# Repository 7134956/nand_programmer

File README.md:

# NANDO (NANDopen) programmer

## General
NANDO is open source NAND programmer based on low cost MCU CH32V307VCT6. It supports parallel NAND, SPI NOR, SPI NAND programming.
High programming speed! For examle EM73C044SNB (1Gb) Write 110(s), Read 80(s).

PCB boards:

Application:

## Features
- USB_HS interface
- PC client software for Linux & Windows.
- TSOP-48 socket for NAND chip
- 8 bit parallel NAND interface
- SPI interface
- 3.3V NAND power supply
- NAND read,write and erase support
- NAND read of chip ID support
- NAND read of bad blocks
- NAND bad block skip option
- NAND include spare area option
- Configurable erase, write, read areas.
- Open KiCad PCB & Schematic
- Open source code
- Read & Write LEDs indication
- Extendable chip database
- Chip autodetection
- Firmware update

### Supported chips
#### Parallel NAND:
K9F2G08U0C, HY27US08121B, TC58NVG2S3E, F59L2G81A, MX30LF2G18AC and others.

See full list of supported chips [qt/nando_parallel_chip_db.csv](qt/nando_parallel_chip_db.csv)

#### SPI NOR flash
AT45DB021D, MX25L8006E, W25Q16JV and others.

See full list of supported chips [qt/nando_spi_nor_db.csv](qt/nando_spi_nor_db.csv)

#### SPI NAND flash
GD5F1GQ4UBxIG, MT29F2G01, F50L2G41LB and others.

See full list of supported chips [qt/nando_spi_nand_db.csv](qt/nando_spi_nand_db.csv)

## Release binaries
...

### License
In general the sorce code, PCB and schematic are under GPLv3 license but with limitations of:

## WiKi
Check [WiKi](https://github.com/bbogush/nand_programmer/wiki) page for more information.

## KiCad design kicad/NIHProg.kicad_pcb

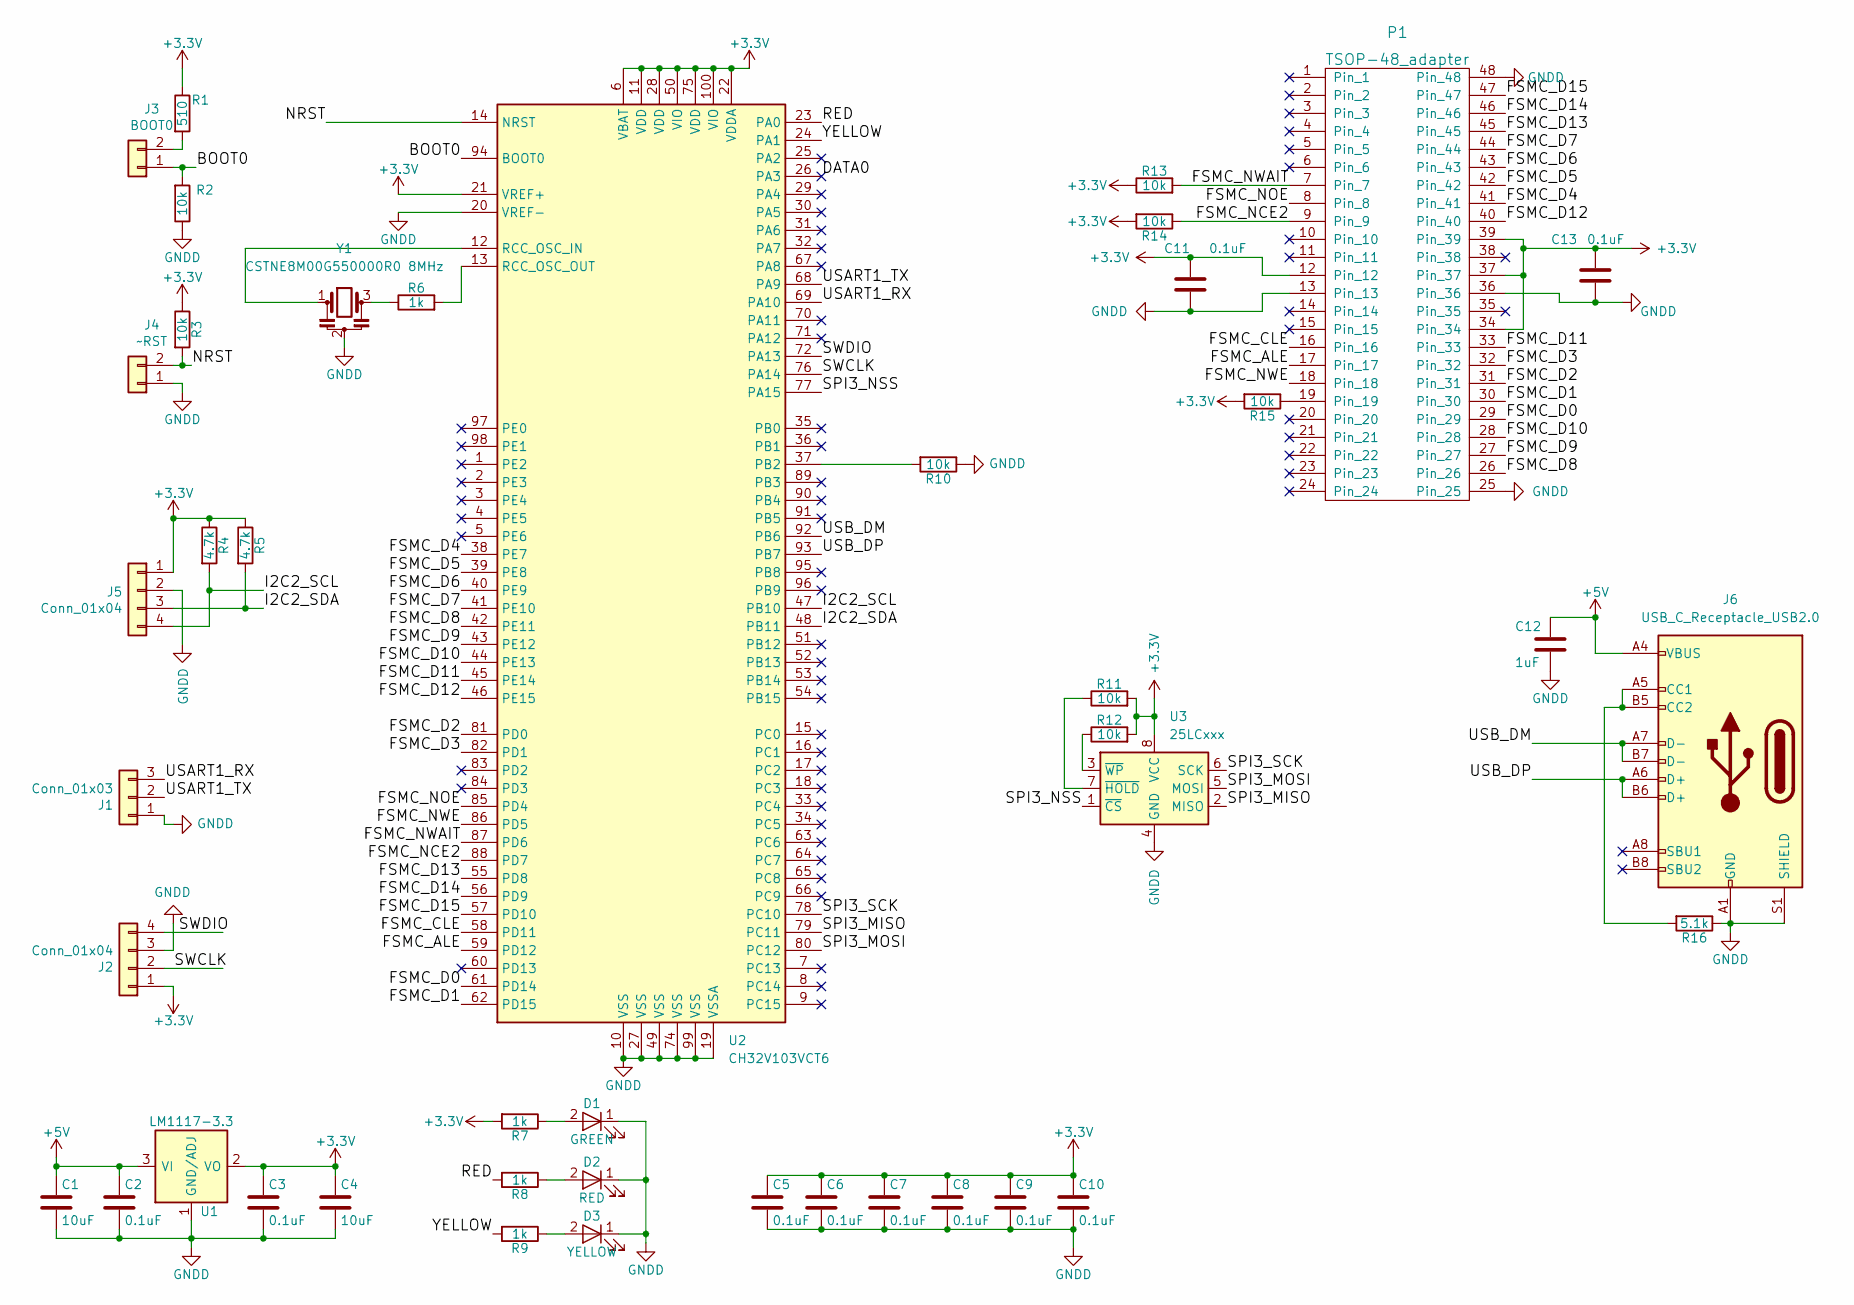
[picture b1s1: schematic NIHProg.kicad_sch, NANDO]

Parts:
C1, C4: 10uF; C_0805_2012Metric_Pad1.18x1.45mm_HandSolder; Farnell Ref 2112850
C2, C3, C5, C6, C7, C8, C9, C10, C11, C13: 0.1uF; C_0603_1608Metric_Pad1.08x0.95mm_HandSolder; Farnell Ref 2320839
C12: 1uF; C_0603_1608Metric_Pad1.08x0.95mm_HandSolder; Farnell Ref 2320839
D1: GREEN; LED_0603_1608Metric_Pad1.05x0.95mm_HandSolder; Farnell Ref 2099239
D2: RED; LED_0603_1608Metric_Pad1.05x0.95mm_HandSolder; Farnell Ref 2099236
D3: YELLOW; LED_0603_1608Metric_Pad1.05x0.95mm_HandSolder; Farnell Ref 2099243
J1: Conn_01x03; PinHeader_1x03_P2.54mm_Vertical; Farnell Ref 3049527
J2, J5: Conn_01x04; PinHeader_1x04_P2.54mm_Vertical; Farnell Ref 3049529
J3: BOOT0; SolderJumper-2_P1.3mm_Open_RoundedPad1.0x1.5mm
J4: ~RST; SolderJumper-2_P1.3mm_Open_RoundedPad1.0x1.5mm
J6: USB_C_Receptacle_USB2.0; TYPE-C-31-M-12; MPN TYPE-C-31-M-17
P1: TSOP-48_adapter; TSOP48ZIF
R1: 510; R_0603_1608Metric_Pad0.98x0.95mm_HandSolder; Farnell Ref 2447679
R2, R3, R10, R11, R12, R13, R14, R15: 10k; R_0603_1608Metric_Pad0.98x0.95mm_HandSolder; Farnell Ref 2447553
R4, R5: 4.7k; R_0603_1608Metric_Pad0.98x0.95mm_HandSolder; Farnell Ref 2447553
R6: 1k; R_0603_1608Metric_Pad0.98x0.95mm_HandSolder; Farnell Ref 2447553
R7, R8, R9: 1k; R_0603_1608Metric_Pad0.98x0.95mm_HandSolder; Farnell Ref 2447587
R16: 5.1k; R_0603_1608Metric_Pad0.98x0.95mm_HandSolder; Farnell Ref 2447587
U1: LM1117-3.3; SOT-223; Farnell Ref 3007498
U2: CH32V103VCT6; LQFP-100_14x14mm_P0.5mm
U3: 25LCxxx; DIP-8_W7.62mm_Socket
Y1: CSTNE8M00G550000R0 8MHz; Resonator_SMD_Murata_CSTxExxV-3Pin_3.0x1.1mm_HandSoldering

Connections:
+3V3: C3.1, C4.1, C5.1, C6.1, C7.1, C8.1, C9.1, C10.1, C11.1, C13.1, J2.1, J5.1, P1.12, P1.34, P1.37, P1.39, R1.1, R3.1, R4.1, R5.1, R7.2, R11.2, R12.2, R13.1, R14.2, R15.2, U1.2 (VO), U1.4 (VO), U2.6 (VBAT), U2.11 (VDD), U2.21 (VREF+), U2.22 (VDDA), U2.28 (VDD), U2.50 (VIO), U2.75 (VDD), U2.100 (VIO), U3.8 (VCC)
+5V: C1.1, C2.1, C12.1, J6.A4 (VBUS), J6.A9 (VBUS), J6.B4 (VBUS), J6.B9 (VBUS), U1.3 (VI)
/BOOT0: J3.1, R2.2, U2.94 (BOOT0)
/DATA0: U2.26 (PA3)
/FSMC_ALE: P1.17, U2.59 (PD12)
/FSMC_CLE: P1.16, U2.58 (PD11)
/FSMC_D0: P1.29, U2.61 (PD14)
/FSMC_D1: P1.30, U2.62 (PD15)
/FSMC_D2: P1.31, U2.81 (PD0)
/FSMC_D3: P1.32, U2.82 (PD1)
/FSMC_D4: P1.41, U2.38 (PE7)
/FSMC_D5: P1.42, U2.39 (PE8)
/FSMC_D6: P1.43, U2.40 (PE9)
/FSMC_D7: P1.44, U2.41 (PE10)
/FSMC_D8: P1.26, U2.42 (PE11)
/FSMC_D9: P1.27, U2.43 (PE12)
/FSMC_D10: P1.28, U2.44 (PE13)
/FSMC_D11: P1.33, U2.45 (PE14)
/FSMC_D12: P1.40, U2.46 (PE15)
/FSMC_D13: P1.45, U2.55 (PD8)
/FSMC_D14: P1.46, U2.56 (PD9)
/FSMC_D15: P1.47, U2.57 (PD10)
/FSMC_NCE2: P1.9, R14.1, U2.88 (PD7)
/FSMC_NOE: P1.8, U2.85 (PD4)
/FSMC_NWAIT: P1.7, R13.2, U2.87 (PD6)
/FSMC_NWE: P1.18, U2.86 (PD5)
/I2C2_SCL: J5.4, R4.2, U2.47 (PB10)
/I2C2_SDA: J5.3, R5.2, U2.48 (PB11)
/NRST: J4.2, R3.2, U2.14 (NRST)
/RED: R8.2, U2.23 (PA0)
/SPI3_MISO: U2.79 (PC11), U3.2 (MISO)
/SPI3_MOSI: U2.80 (PC12), U3.5 (MOSI)
/SPI3_NSS: U2.77 (PA15), U3.1 (~CS)
/SPI3_SCK: U2.78 (PC10), U3.6 (SCK)
/SWCLK: J2.2, U2.76 (PA14)
/SWDIO: J2.4, U2.72 (PA13)
/USART1_RX: J1.3, U2.69 (PA10)
/USART1_TX: J1.2, U2.68 (PA9)
/USB_DM: J6.A7 (D-), J6.B7 (D-), U2.92 (PB6)
/USB_DP: J6.A6 (D+), J6.B6 (D+), U2.93 (PB7)
/YELLOW: R9.2, U2.24 (PA1)
GNDD: C1.2, C2.2, C3.2, C4.2, C5.2, C6.2, C7.2, C8.2, C9.2, C10.2, C11.2, C12.2, C13.2, D1.1 (K), D2.1 (K), D3.1 (K), J1.1, J2.3, J4.1, J5.2, J6.A1 (GND), J6.A12 (GND), J6.B1 (GND), J6.B12 (GND), J6.S1 (SHIELD), P1.13, P1.25, P1.36, P1.48, R2.1, R10.1, R16.1, U1.1 (GND/ADJ), U2.10 (VSS), U2.19 (VSSA), U2.20 (VREF-), U2.27 (VSS), U2.49 (VSS), U2.74 (VSS), U2.99 (VSS), U3.4 (GND), Y1.2
unnamed: D1.2 (A), R7.1
unnamed: D2.2 (A), R8.1
unnamed: D3.2 (A), R9.1
unnamed: J3.2, R1.2
unnamed: J6.A5 (CC1), J6.B5 (CC2), R16.2
unnamed: P1.19, R15.1
unnamed: R6.1, Y1.3
unnamed: R6.2, U2.13 (RCC_OSC_OUT)
unnamed: R10.2, U2.37 (PB2)
unnamed: R11.1, U3.7 (~HOLD)
unnamed: R12.1, U3.3 (~WP)
unnamed: U2.12 (RCC_OSC_IN), Y1.1

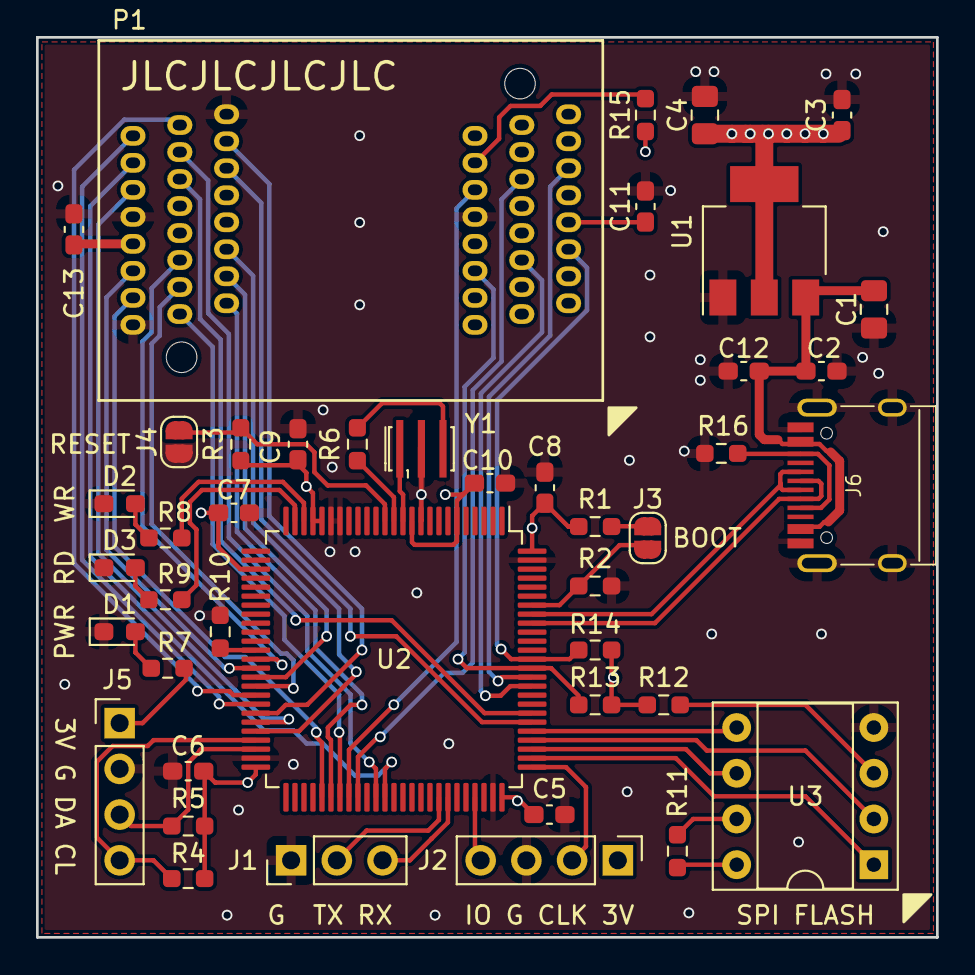
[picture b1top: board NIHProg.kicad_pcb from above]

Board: 4 copper layers, 50.0 x 50.0 mm, 43 parts (0 on the bottom side), 53 nets.

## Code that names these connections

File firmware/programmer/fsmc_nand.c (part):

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    RCC_APB2PeriphClockCmd(RCC_APB2Periph_GPIOD | RCC_APB2Periph_GPIOE, ENABLE);

    gpio_init.GPIO_Pin =
		GPIO_Pin_0		//FSMC_D2
		| GPIO_Pin_1	//FSMC_D3
		| GPIO_Pin_4	//FSMC_NOE
		| GPIO_Pin_5	//FSMC_NWE
		| GPIO_Pin_7	//FSMC_NCE2
		| GPIO_Pin_8	//FSMC_D13
		| GPIO_Pin_9	//FSMC_D14
		| GPIO_Pin_10	//FSMC_D15
		| GPIO_Pin_11	//FSMC_CLE
		| GPIO_Pin_12	//FSMC_ALE
		| GPIO_Pin_14	//FSMC_D0
		| GPIO_Pin_15;	//FSMC_D1
    gpio_init.GPIO_Speed = GPIO_Speed_50MHz;
    gpio_init.GPIO_Mode = GPIO_Mode_AF_PP;
    GPIO_Init(GPIOD, &gpio_init);


    gpio_init.GPIO_Pin =
		GPIO_Pin_7		//FSMC_D4
		| GPIO_Pin_8	//FSMC_D5
		| GPIO_Pin_9	//FSMC_D6
		| GPIO_Pin_10	//FSMC_D7
		| GPIO_Pin_11	//FSMC_D8
		| GPIO_Pin_12	//FSMC_D9
		| GPIO_Pin_13	//FSMC_D10
		| GPIO_Pin_14	//FSMC_D11
		| GPIO_Pin_15;	//FSMC_D12
    GPIO_Init(GPIOE, &gpio_init);

    /* NWAIT NAND pin configuration */
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
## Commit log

2022-11-04 Port on CH32V307 chip for USB HS support.
2022-11-05 Extend np_send_write_ack for 64-bit size.
2022-11-05 Add check buffer overflow.
2022-11-05 Increase the page buffer.
2022-11-05 Qt: Fix for Qt 6.4.0 + MinGW64
2022-11-12 KiCad: Update schematic and board for CH32V307VCT6 MCU.
2023-02-18 Qt: Add flash work range support.
    Qt: Fix progress in part mode
2023-02-20 firmware: Change SPI1 to SPI3 for new board design.
2023-02-24 firmware: update vendor code.
2023-02-24 README: Update.
2023-02-24 firmware: Update CherryUSB library to latest version.
2023-02-24 DB: SPI: Add W25Q64FV chip.
2023-04-15 firmware: Fix typos in debug messages. Unused include in main.c
2023-04-15 CherryUSB: Update USB library
2023-04-15 firmware: Fix USB collision.
2023-04-15 Add SPI NAND flash support.
2023-04-15 Qt: fix compile error when ODR check enabled.
    when two structs with the same name, the linker many be confused. when
    LTO
    is enabled, ODR checked is required.
2023-04-16 Firmware: Use DMA for SPI transfer.
2023-04-16 Qt: Add "verify" action.
2024-11-17 DB: Adding chips and sorting.

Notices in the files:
firmware/programmer/fsmc_nand.c:
Copyright (C) 2020 NANDO authors
This program is free software; you can redistribute it and/or modify
it under the terms of the GNU General Public License version 3.
